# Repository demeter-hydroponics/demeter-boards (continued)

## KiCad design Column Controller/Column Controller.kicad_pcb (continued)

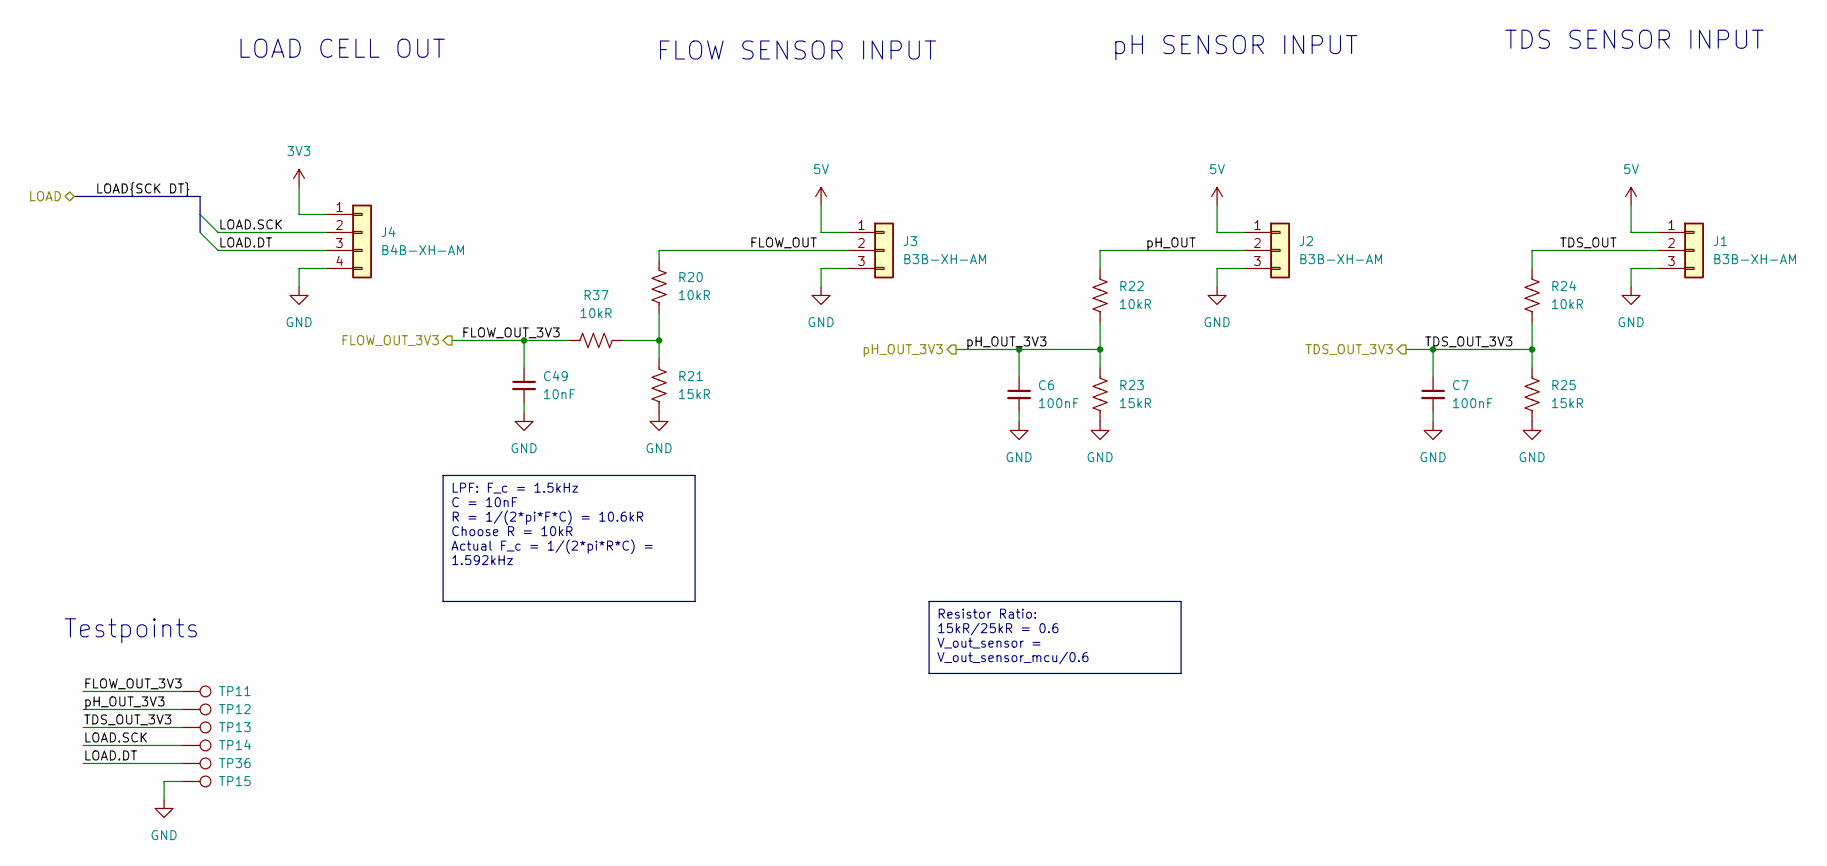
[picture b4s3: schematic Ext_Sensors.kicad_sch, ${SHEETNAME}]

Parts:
C6, C7: 100nF; C_0603_1608Metric; Part Number CL31B104KCFNNNE
C49: 10nF; C_0402_1005Metric; Part Number CL05B103KO5NNNC
J1, J2, J3: B3B-XH-AM; JST_XH_B3B-XH-AM_1x03_P2.50mm_Vertical; Part Number B3B-XH-AM
J4: B4B-XH-AM; JST_XH_B4B-XH-AM_1x04_P2.50mm_Vertical; Part Number B4B-XH-AM
R20, R22, R24, R37: 10kR; R_0603_1608Metric; Part Number RC0603FR-0710KL
R21, R23, R25: 15kR; R_0603_1608Metric; Part Number RC0603FR-0715KL
TP11, TP12, TP13, TP14, TP15, TP36: TestPoint_Pad_D1.0mm

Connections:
3V3: J4.1; also elsewhere on the board
5V: J1.1, J2.1, J3.1; also elsewhere on the board
/Ext Sensors/FLOW_OUT: J3.2, R20.1
/Ext Sensors/FLOW_OUT_3V3: C49.1, R37.1, TP11.1; also elsewhere on the board
/Ext Sensors/LOAD.DT: J4.3, TP36.1; also elsewhere on the board
/Ext Sensors/LOAD.SCK: J4.2, TP14.1; also elsewhere on the board
/Ext Sensors/TDS_OUT: J1.2, R24.1
/Ext Sensors/TDS_OUT_3V3: C7.1, R24.2, R25.1, TP13.1; also elsewhere on the board
/Ext Sensors/pH_OUT: J2.2, R22.1
/Ext Sensors/pH_OUT_3V3: C6.1, R22.2, R23.1, TP12.1; also elsewhere on the board
GND: C6.2, C7.2, C49.2, J1.3, J2.3, J3.3, J4.4, R21.2, R23.2, R25.2, TP15.1; also elsewhere on the board
unnamed: R20.2, R21.1, R37.2

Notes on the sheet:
LPF: F_c = 1.5kHz C = 10nF R = 1/(2*pi*F*C) = 10.6kR Choose R = 10kR Actual F_c = 1/(2*pi*R*C) = 1.592kHz
Resistor Ratio: 15kR/25kR = 0.6 V_out_sensor = V_out_sensor_mcu/0.6
Testpoints
pH SENSOR INPUT
FLOW SENSOR INPUT
LOAD CELL OUT
TDS SENSOR INPUT

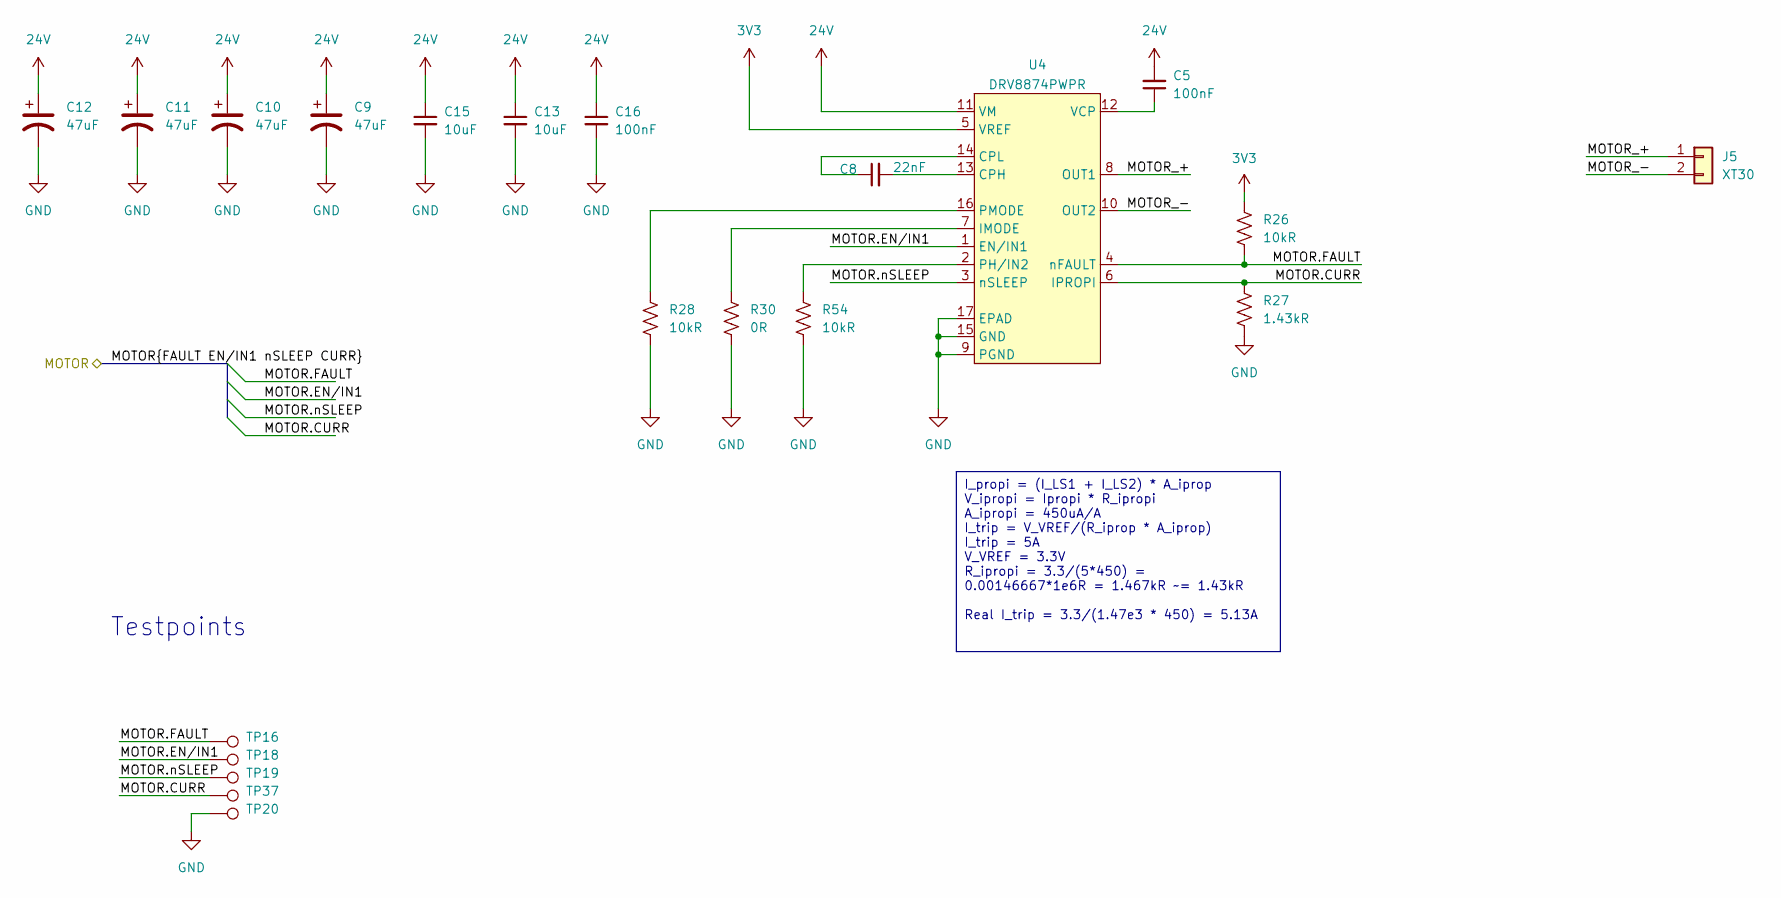
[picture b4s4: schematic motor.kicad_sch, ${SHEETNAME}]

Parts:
C5, C16: 100nF; C_0402_1005Metric; Part Number CL31B104KCFNNNE
C8: 22nF; C_0603_1608Metric
C9, C10, C11, C12: 47uF; CP_Radial_D8.0mm_P3.50mm; Part Number ECA-2AM470BJ
C13, C15: 10uF; C_1210_3225Metric; Part Number CL32B106KMVNNWE
J5: XT30
R26, R28, R54: 10kR; R_0603_1608Metric; Part Number RC0603FR-0710KL
R27: 1.43kR; R_0603_1608Metric; Part Number RC0603FR-071K43L
R30: 0R; R_0603_1608Metric; Part Number RC0603FR-070RL
TP16, TP18, TP19, TP20, TP37: TestPoint_Pad_D1.0mm
U4: DRV8874PWPR; DRV8874; Part Number DRV8874PWPR

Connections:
3V3: R26.1, U4.5 (VREF); also elsewhere on the board
24V: C5.2, C9.1, C10.1, C11.1, C12.1, C13.1, C15.1, C16.1, U4.11 (VM); also elsewhere on the board
/Microcontroller/MOTOR_2.CURR: R27.1, TP37.1, U4.6 (IPROPI); also elsewhere on the board
/Microcontroller/MOTOR_2.EN/IN1: TP18.1, U4.1 (EN/IN1); also elsewhere on the board
/Microcontroller/MOTOR_2.FAULT: R26.2, TP16.1, U4.4 (nFAULT); also elsewhere on the board
/Microcontroller/MOTOR_2.nSLEEP: TP19.1, U4.3 (nSLEEP); also elsewhere on the board
/Motor Controller 2/MOTOR_+: J5.1, U4.8 (OUT1)
/Motor Controller 2/MOTOR_-: J5.2, U4.10 (OUT2)
GND: C9.2, C10.2, C11.2, C12.2, C13.2, C15.2, C16.2, R27.2, R28.2, R30.2, R54.2, TP20.1, U4.9 (PGND), U4.15 (GND), U4.17 (EPAD); also elsewhere on the board
unnamed: C8.2, U4.13 (CPH)
unnamed: C8.1, U4.14 (CPL)
unnamed: R30.1, U4.7 (IMODE)
unnamed: R54.1, U4.2 (PH/IN2)
unnamed: R28.1, U4.16 (PMODE)
unnamed: C5.1, U4.12 (VCP)

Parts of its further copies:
C37, C38: 100nF; C_0402_1005Metric; Part Number CL31B104KCFNNNE
C39, C40, C41, C42: 47uF; CP_Radial_D8.0mm_P3.50mm; Part Number ECA-2AM470BJ
C43, C44: 10uF; C_1210_3225Metric; Part Number CL32B106KMVNNWE
C46: 22nF; C_0603_1608Metric
J9: XT30
R29, R55, R58: 10kR; R_0603_1608Metric; Part Number RC0603FR-0710KL
R60: 0R; R_0603_1608Metric; Part Number RC0603FR-070RL
R61: 1.43kR; R_0603_1608Metric; Part Number RC0603FR-071K43L
TP21, TP23, TP24, TP25, TP38: TestPoint_Pad_D1.0mm
U10: DRV8874PWPR; DRV8874; Part Number DRV8874PWPR

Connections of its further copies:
3V3: R58.1, U10.5 (VREF); also elsewhere on the board
24V: C37.2, C38.1, C39.1, C40.1, C41.1, C42.1, C43.1, C44.1, U10.11 (VM); also elsewhere on the board
/Microcontroller/MOTOR_1.CURR: R61.1, TP38.1, U10.6 (IPROPI); also elsewhere on the board
/Microcontroller/MOTOR_1.EN/IN1: TP23.1, U10.1 (EN/IN1); also elsewhere on the board
/Microcontroller/MOTOR_1.FAULT: R58.2, TP21.1, U10.4 (nFAULT); also elsewhere on the board
/Microcontroller/MOTOR_1.nSLEEP: TP24.1, U10.3 (nSLEEP); also elsewhere on the board
/Motor Controller 1/MOTOR_+: J9.1, U10.8 (OUT1)
/Motor Controller 1/MOTOR_-: J9.2, U10.10 (OUT2)
GND: C38.2, C39.2, C40.2, C41.2, C42.2, C43.2, C44.2, R29.2, R55.2, R60.2, R61.2, TP25.1, U10.9 (PGND), U10.15 (GND), U10.17 (EPAD); also elsewhere on the board
unnamed: C46.2, U10.13 (CPH)
unnamed: C46.1, U10.14 (CPL)
unnamed: R60.1, U10.7 (IMODE)
unnamed: R55.1, U10.2 (PH/IN2)
unnamed: R29.1, U10.16 (PMODE)
unnamed: C37.1, U10.12 (VCP)

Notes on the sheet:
I_propi = (I_LS1 + I_LS2) * A_iprop V_ipropi = Ipropi * R_ipropi A_ipropi = 450uA/A I_trip = V_VREF/(R_iprop * A_iprop) I_trip = 5A V_VREF = 3.3V R_ipropi = 3.3/(5*450) = 0.00146667*1e6R = 1.467kR ~= 1.43kR Real I_trip = 3.3/(1.47e3 * 450) = 5.13A
Testpoints

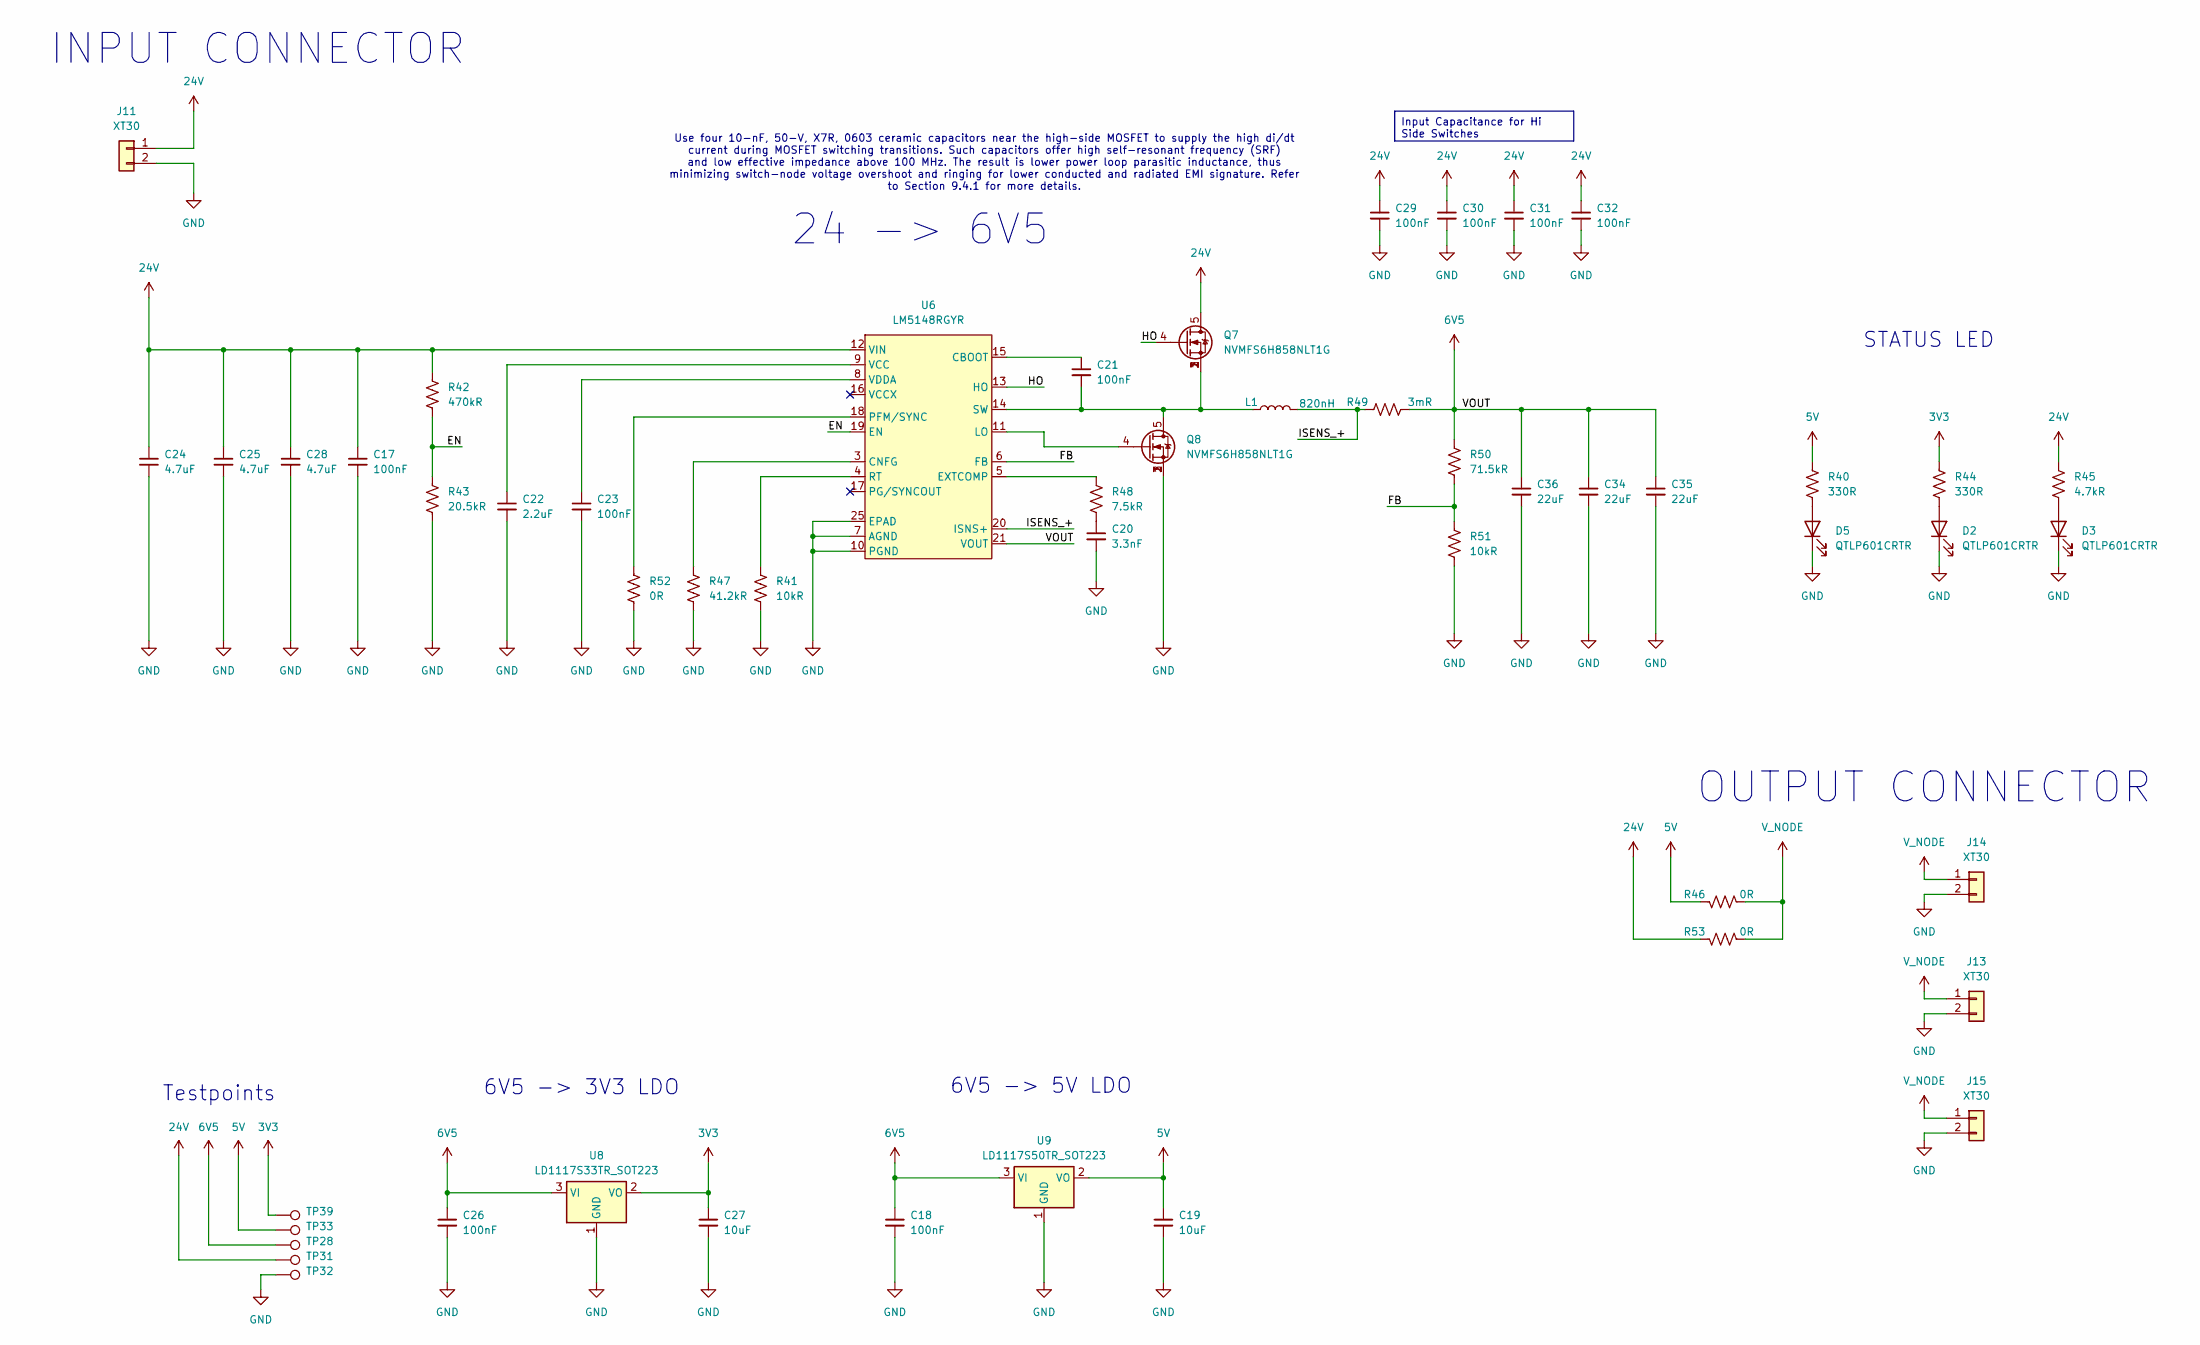
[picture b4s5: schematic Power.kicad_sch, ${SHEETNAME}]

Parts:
C17, C21, C23, C29, C30, C31, C32: 100nF; C_0402_1005Metric; Part Number CL31B104KCFNNNE
C18, C26: 100nF; C_1206_3216Metric; Part Number CL31B104KCFNNNE
C19, C27: 10uF; C_1210_3225Metric; Part Number CL32B106KMVNNWE
C20: 3.3nF; C_0402_1005Metric; Part Number CL05B332KA5VPNC
C22: 2.2uF; C_0603_1608Metric; Part Number GRM188R61H225KE11D
C24, C25, C28: 4.7uF; C_1210_3225Metric; Part Number CL32Y475MCIVPNE
C34, C35, C36: 22uF; C_0805_2012Metric; Part Number CL21A226MAYNNNE
D2, D3, D5: QTLP601CRTR; LED_0603_1608Metric; Part Number QTLP601CRTR
J11, J13, J14, J15: XT30; Part Number XT30
L1: 820nH; SRP7050; Part Number SRP7050TA-R82M
Q7, Q8: NVMFS6H858NLT1G; NVMFS6H858NL
R40, R44: 330R; R_0402_1005Metric; Part Number RC0603FR-07330RL
R41, R51: 10kR; R_0603_1608Metric; Part Number RC0603FR-0710KL
R42: 470kR; R_0603_1608Metric; Part Number RC0603FR-07470KL
R43: 20.5kR; R_0603_1608Metric; Part Number RC0603FR-0720K5L
R45: 4.7kR; R_0603_1608Metric; Part Number RC0603FR-074K7L
R46, R52, R53: 0R; R_0603_1608Metric; Part Number RC0603FR-070RL
R47: 41.2kR; R_0603_1608Metric; Part Number RC0603FR-0741K2L
R48: 7.5kR; R_0603_1608Metric; Part Number RC0603FR-077K5L
R49: 3mR; R_0805_2012Metric; Part Number PA0805FRF070R003L
R50: 71.5kR; R_0603_1608Metric; Part Number RC0603FR-0771K5L
TP28, TP31, TP32, TP33, TP39: TestPoint_Pad_D1.0mm
U6: LM5148RGYR; LM5148
U8: LD1117S33TR_SOT223; SOT-223-3_TabPin2; Part Number LD1117S33TR_SOT223
U9: LD1117S50TR_SOT223; SOT-223-3_TabPin2; Part Number LD1117S50TR_SOT223

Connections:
3V3: C27.1, R44.2, TP39.1, U8.2 (VO); also elsewhere on the board
5V: C19.1, R40.2, R46.2, TP33.1, U9.2 (VO); also elsewhere on the board
6V5: C18.1, C26.1, C34.1, C35.1, C36.1, R49.2, R50.2, TP28.1, U6.21 (VOUT), U8.3 (VI), U9.3 (VI)
24V: C17.1, C24.1, C25.1, C28.1, C29.1, C30.1, C31.1, C32.1, J11.1, Q7.5, R42.2, R45.2, R53.2, TP31.1, U6.12 (VIN); also elsewhere on the board
/Power/EN: R42.1, R43.2, U6.19 (EN)
/Power/FB: R50.1, R51.2, U6.6 (FB)
/Power/HO: Q7.4, U6.13 (HO)
/Power/ISENS_+: L1.2, R49.1, U6.20 (ISNS+)
GND: C17.2, C18.2, C19.2, C20.2, C22.2, C23.2, C24.2, C25.2, C26.2, C27.2, C28.2, C29.2, C30.2, C31.2, C32.2, C34.2, C35.2, C36.2, D2.1 (K), D3.1 (K), D5.1 (K), J11.2, J13.2, J14.2, J15.2, Q8.1, Q8.2, Q8.3, R41.1, R43.1, R47.1, R51.1, R52.1, TP32.1, U6.7 (AGND), U6.10 (PGND), U6.25 (EPAD), U8.1 (GND), U9.1 (GND); also elsewhere on the board
unnamed: C20.1, R48.1
unnamed: D2.2 (A), R44.1
unnamed: D3.2 (A), R45.1
unnamed: D5.2 (A), R40.1
unnamed: C21.1, U6.15 (CBOOT)
unnamed: R47.2, U6.3 (CNFG)
unnamed: R48.2, U6.5 (EXTCOMP)
unnamed: Q8.4, U6.11 (LO)
unnamed: R52.2, U6.18 (PFM/SYNC)
unnamed: R41.2, U6.4 (RT)
unnamed: C21.2, L1.1, Q7.1, Q7.2, Q7.3, Q8.5, U6.14 (SW)
unnamed: C22.1, U6.9 (VCC)
unnamed: C23.1, U6.8 (VDDA)
V_NODE: J13.1, J14.1, J15.1, R46.1, R53.1

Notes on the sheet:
Input Capacitance for Hi Side Switches
Use four 10-nF, 50-V, X7R, 0603 ceramic capacitors near the high-side MOSFET to supply the high di/dt current during MOSFET switching transitions. Such capacitors offer high self-resonant frequency (SRF) and low effective impedance above 100 MHz. The result is lower power loop parasitic inductance,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
Testpoints
6V5 -> 3V3 LDO
OUTPUT CONNECTOR
INPUT CONNECTOR
24 -> 6V5
STATUS LED
6V5 -> 5V LDO

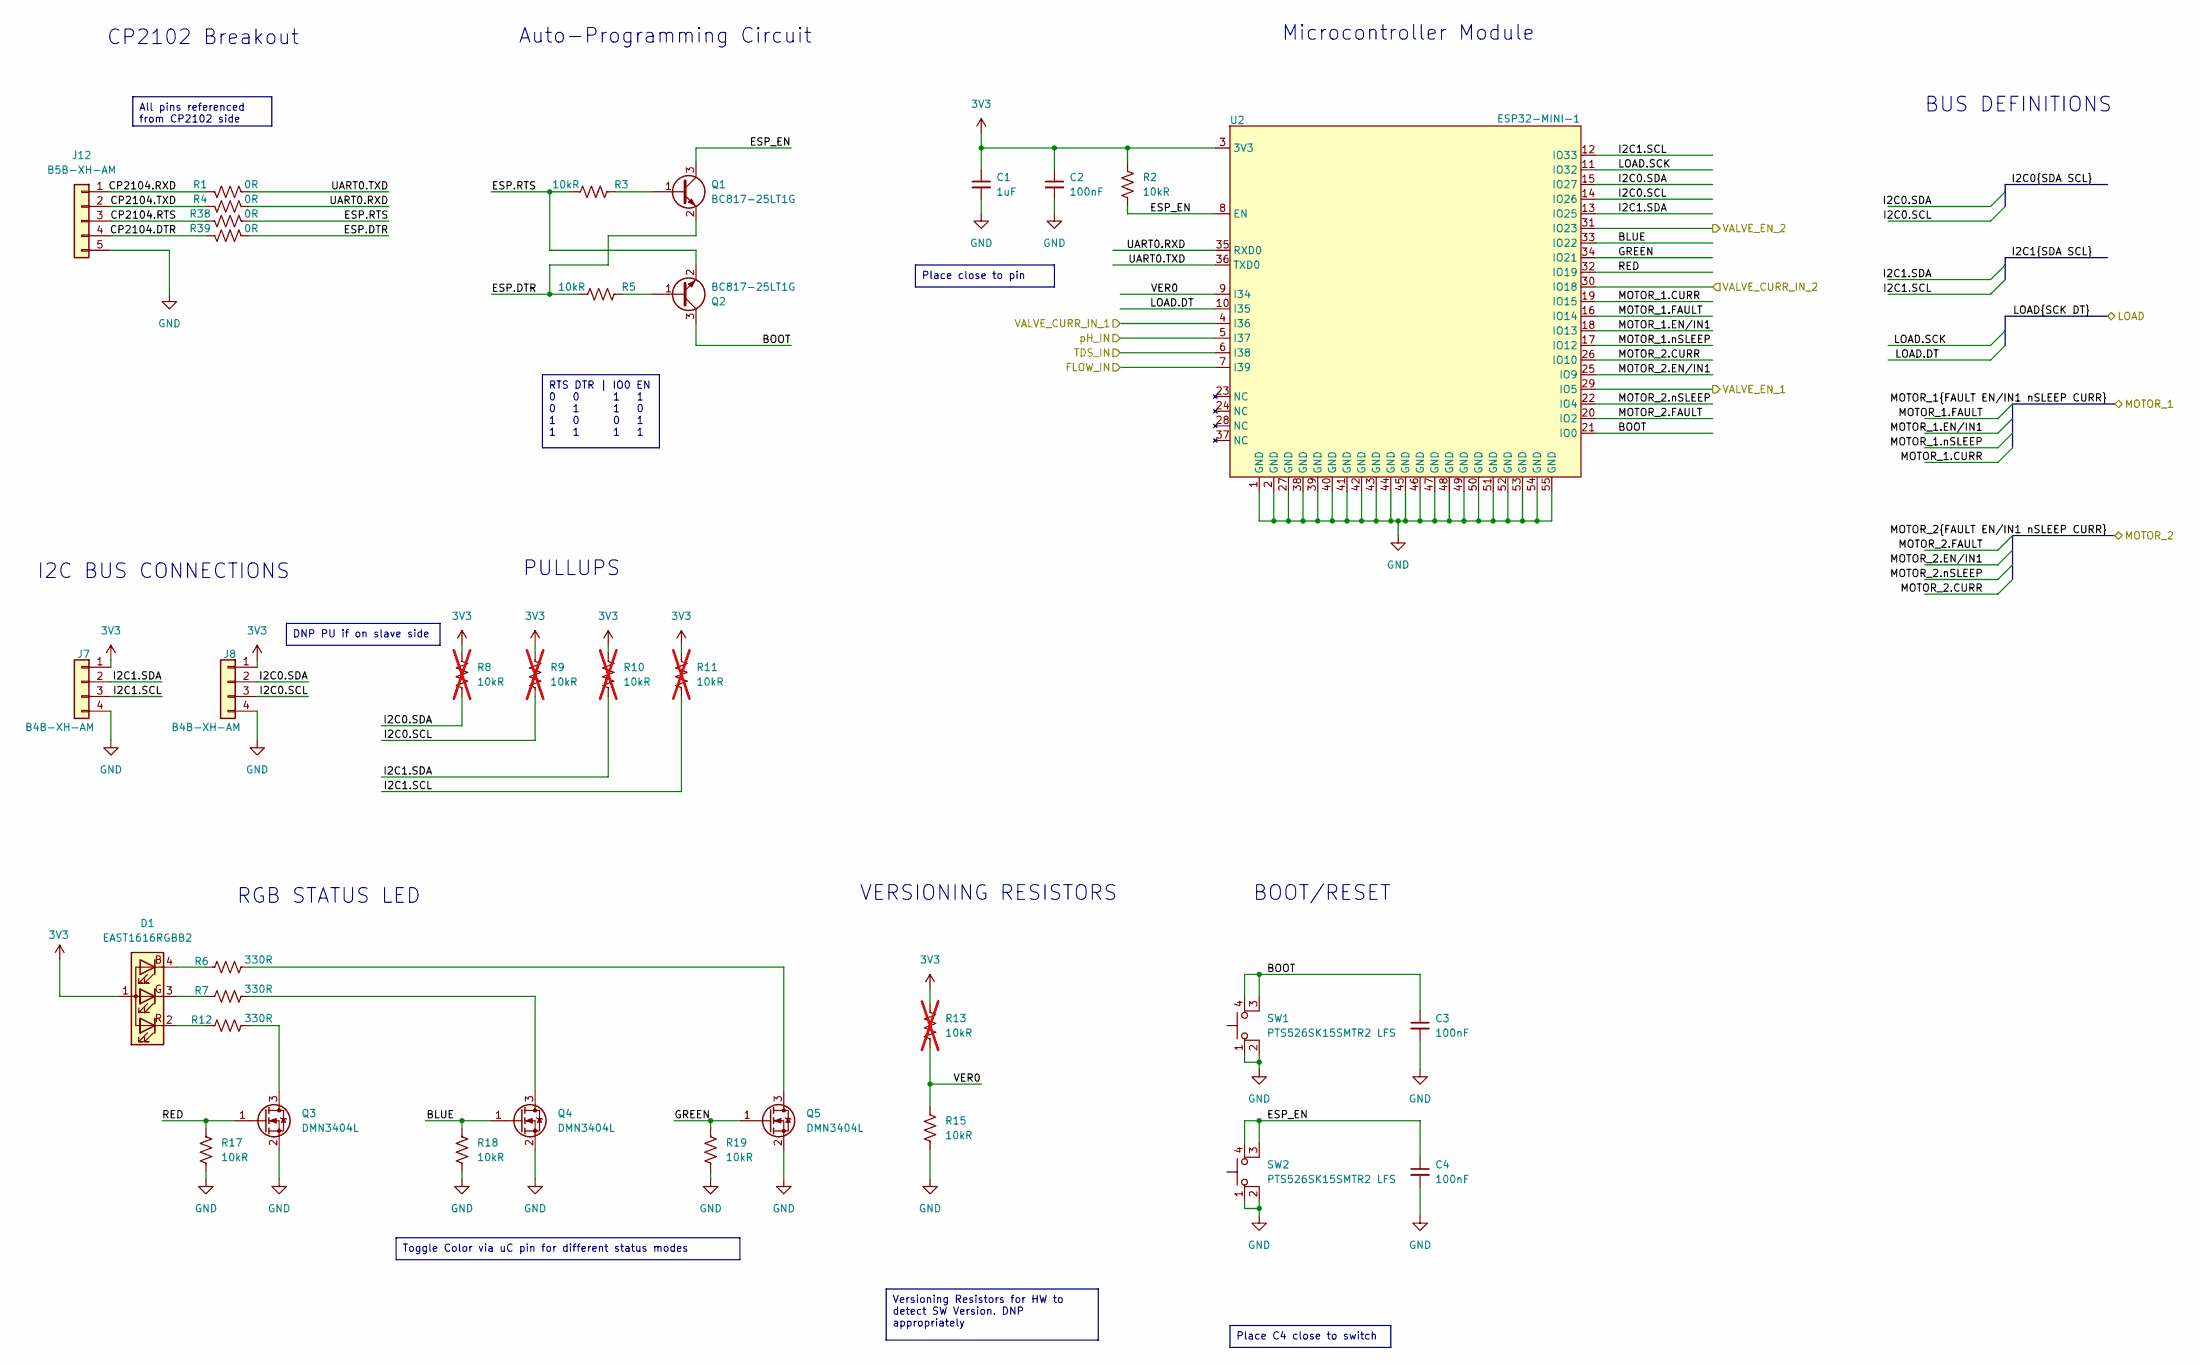
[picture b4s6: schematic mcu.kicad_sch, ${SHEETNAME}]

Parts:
C1: 1uF; C_1206_3216Metric; Part Number CL31B105KCHNNNE
C2, C3, C4: 100nF; C_1206_3216Metric; Part Number CL31B104KCFNNNE
D1: EAST1616RGBB2; Part Number EAST1616RGBB2
J7, J8: B4B-XH-AM; JST_XH_B4B-XH-AM_1x04_P2.50mm_Vertical; Part Number B4B-XH-AM
J12: B5B-XH-AM; JST_XH_B5B-XH-AM_1x05_P2.50mm_Vertical
Q1, Q2: BC817-25LT1G; SOT-23; Part Number BC817-25LT1G
Q3, Q4, Q5: DMN3404L; SOT-23; Part Number DMN3404L
R1, R4, R38, R39: 0R; R_0603_1608Metric; Part Number RC0603FR-070RL
R2, R3, R5, R15, R17, R18, R19: 10kR; R_0603_1608Metric; Part Number RC0603FR-0710KL
R6, R7, R12: 330R; R_0402_1005Metric; Part Number RC0603FR-07330RL
R8, R9, R10, R11, R13: 10kR; R_0603_1608Metric; Part Number RC0603FR-0710KL; not fitted
SW1, SW2: PTS526SK15SMTR2 LFS; Part Number PTS526SK15SMTR2 LFS
U2: ESP32-MINI-1

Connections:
3V3: C1.1, C2.1, D1.1 (A), J7.1, J8.1, R2.1, R8.1, R9.1, R10.1, R11.1, R13.1, U2.3 (3V3); also elsewhere on the board
/Ext Sensors/FLOW_OUT_3V3: U2.7 (I39); also elsewhere on the board
/Ext Sensors/LOAD.DT: U2.10 (I35); also elsewhere on the board
/Ext Sensors/LOAD.SCK: U2.11 (IO32); also elsewhere on the board
/Ext Sensors/TDS_OUT_3V3: U2.6 (I38); also elsewhere on the board
/Ext Sensors/pH_OUT_3V3: U2.5 (I37); also elsewhere on the board
/Microcontroller/BLUE: Q4.1 (G), R18.1, U2.33 (IO22)
/Microcontroller/BOOT: C3.1, Q2.3 (C), SW1.3 (K), SW1.4 (A), U2.21 (IO0)
/Microcontroller/CP2104.DTR: J12.4, R39.2
/Microcontroller/CP2104.RTS: J12.3, R38.2
/Microcontroller/CP2104.RXD: J12.1, R1.2
/Microcontroller/CP2104.TXD: J12.2, R4.2
/Microcontroller/ESP.DTR: Q1.2 (E), R5.1, R39.1
/Microcontroller/ESP.RTS: Q2.2 (E), R3.1, R38.1
/Microcontroller/ESP_EN: C4.1, Q1.3 (C), R2.2, SW2.3 (K), SW2.4 (A), U2.8 (EN)
/Microcontroller/GREEN: Q5.1 (G), R19.1, U2.34 (IO21)
/Microcontroller/I2C0.SCL: J8.3, R9.2, U2.14 (IO26)
/Microcontroller/I2C0.SDA: J8.2, R8.2, U2.15 (IO27)
/Microcontroller/I2C1.SCL: J7.3, R11.2, U2.12 (IO33)
/Microcontroller/I2C1.SDA: J7.2, R10.2, U2.13 (IO25)
/Microcontroller/MOTOR_1.CURR: U2.19 (IO15); also elsewhere on the board
/Microcontroller/MOTOR_1.EN/IN1: U2.18 (IO13); also elsewhere on the board
/Microcontroller/MOTOR_1.FAULT: U2.16 (IO14); also elsewhere on the board
/Microcontroller/MOTOR_1.nSLEEP: U2.17 (IO12); also elsewhere on the board
/Microcontroller/MOTOR_2.CURR: U2.26 (IO10); also elsewhere on the board
/Microcontroller/MOTOR_2.EN/IN1: U2.25 (IO9); also elsewhere on the board
/Microcontroller/MOTOR_2.FAULT: U2.20 (IO2); also elsewhere on the board
/Microcontroller/MOTOR_2.nSLEEP: U2.22 (IO4); also elsewhere on the board
/Microcontroller/RED: Q3.1 (G), R17.1, U2.32 (IO19)
/Microcontroller/UART0.RXD: R4.1, U2.35 (RXD0)
/Microcontroller/UART0.TXD: R1.1, U2.36 (TXD0)
/Microcontroller/VER0: R13.2, R15.1, U2.9 (I34)
/Relay Controller 1/CURR_OUT: U2.4 (I36); also elsewhere on the board
/Relay Controller 1/RELAY_IN: U2.29 (IO5); also elsewhere on the board
/Relay Controller 2/CURR_OUT: U2.30 (IO18); also elsewhere on the board
/Relay Controller 2/RELAY_IN: U2.31 (IO23); also elsewhere on the board
GND: C1.2, C2.2, C3.2, C4.2, J7.4, J8.4, J12.5, Q3.2 (S), Q4.2 (S), Q5.2 (S), R15.2, R17.2, R18.2, R19.2, SW1.1, SW1.2, SW2.1, SW2.2, U2.1 (GND), U2.2 (GND), U2.27 (GND), U2.38 (GND), U2.39 (GND), U2.40 (GND), U2.41 (GND), U2.42 (GND), U2.43 (GND), U2.44 (GND), U2.45 (GND), U2.46 (GND), U2.47 (GND), U2.48 (GND), U2.49 (GND), U2.50 (GND), U2.51 (GND), U2.52 (GND), U2.53 (GND), U2.54 (GND), U2.55 (GND); also elsewhere on the board
unnamed: D1.4 (BK), R6.1
unnamed: D1.3 (GK), R7.1
unnamed: D1.2 (RK), R12.1
unnamed: Q1.1 (B), R3.2
unnamed: Q2.1 (B), R5.2
unnamed: Q3.3 (D), R12.2
unnamed: Q4.3 (D), R7.2
unnamed: Q5.3 (D), R6.2

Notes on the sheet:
DNP PU if on slave side
All pins referenced from CP2102 side
Versioning Resistors for HW to detect SW Version. DNP appropriately
RTS DTR | IO0 EN 0 0 1 1 0 1 1 0 1 0 0 1 1 1 1 1
Toggle Color via uC pin for different status modes
Place C4 close to switch
Place close to pin
I2C BUS CONNECTIONS
VERSIONING RESISTORS
RGB STATUS LED
Microcontroller Module
PULLUPS
Auto-Programming Circuit
CP2102 Breakout
BUS DEFINITIONS
BOOT/RESET

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
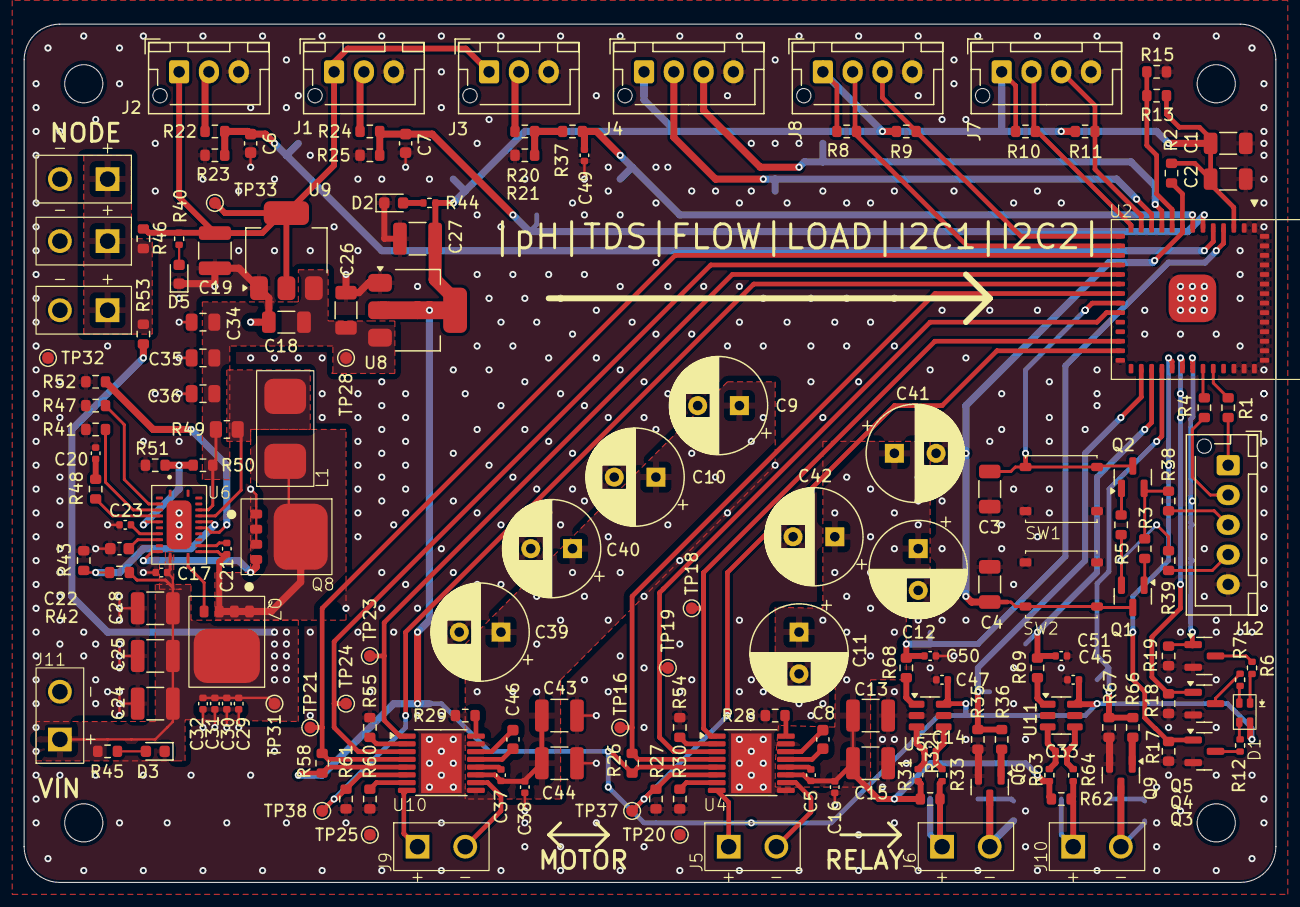
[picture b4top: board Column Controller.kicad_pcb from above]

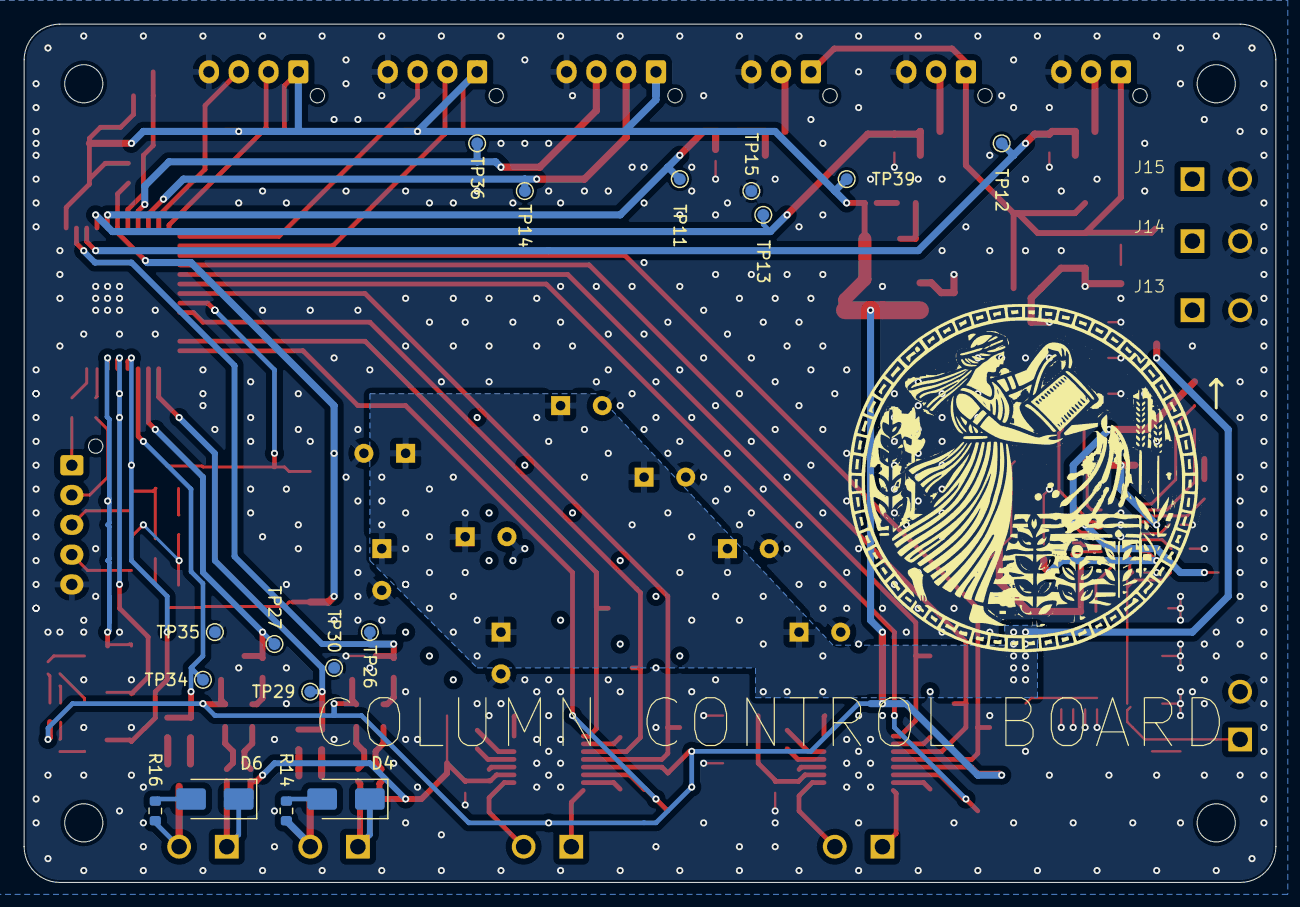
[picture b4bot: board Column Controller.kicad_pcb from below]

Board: 4 copper layers, 105.0 x 72.0 mm, 186 parts (17 on the bottom side), 100 nets.

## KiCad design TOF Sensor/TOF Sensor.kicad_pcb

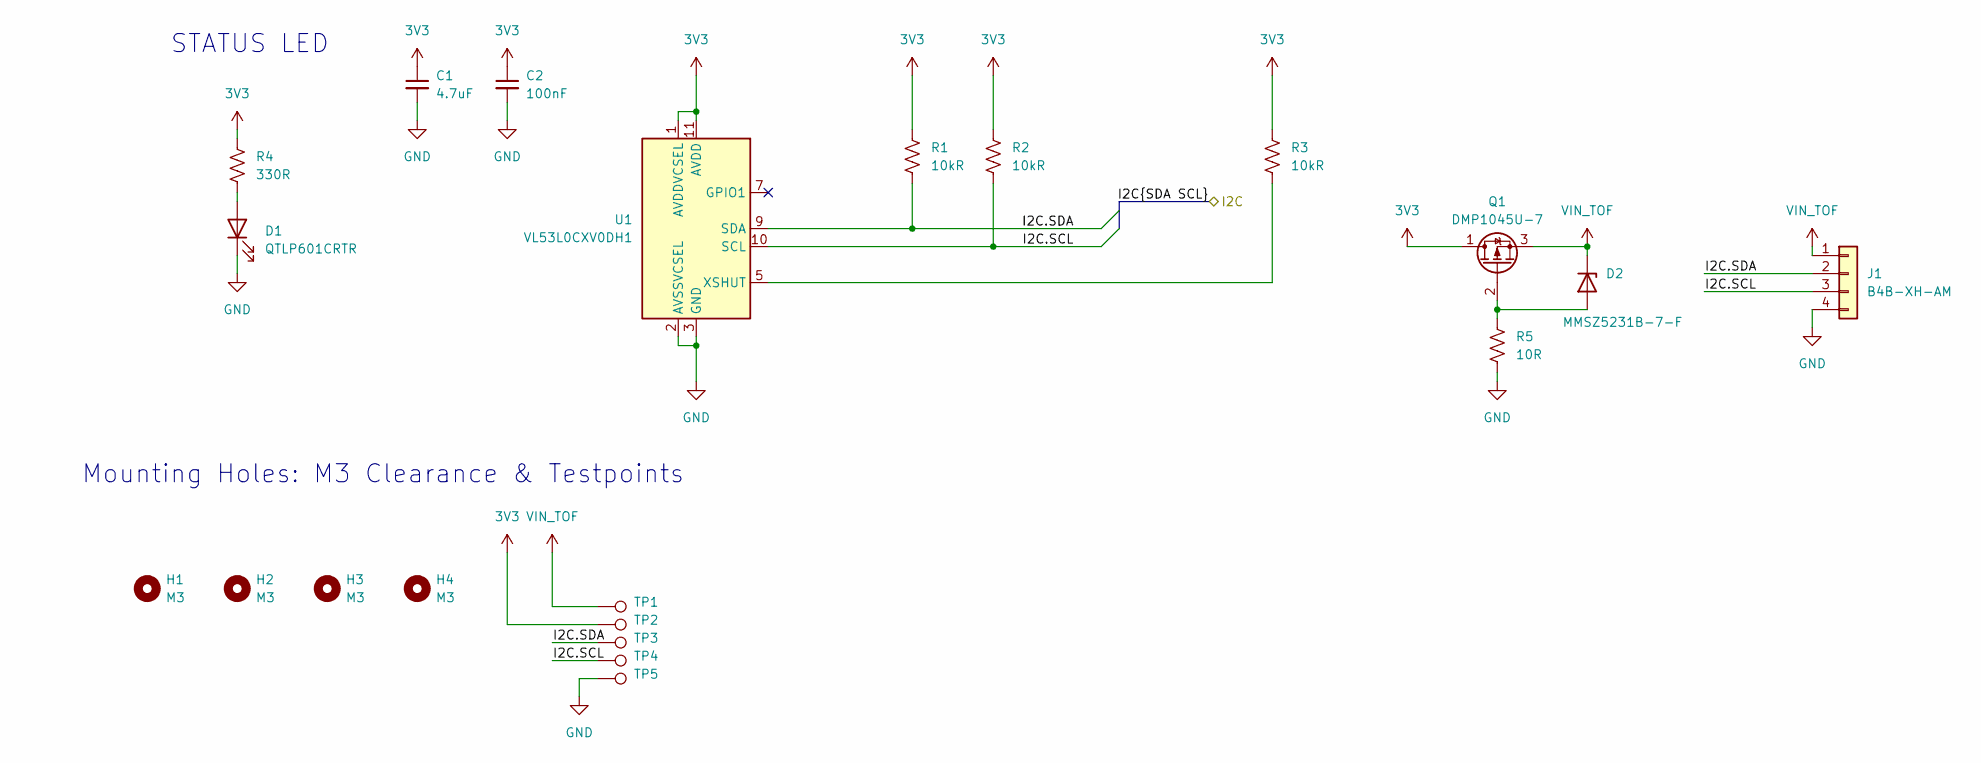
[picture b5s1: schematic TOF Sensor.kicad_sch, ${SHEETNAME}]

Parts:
C1: 4.7uF; C_1210_3225Metric; Part Number CL32Y475MCIVPNE
C2: 100nF; C_1206_3216Metric; Part Number CL31B104KCFNNNE
D1: QTLP601CRTR; LED_0603_1608Metric; Part Number QTLP601CRTR
D2: MMSZ5231B-7-F; D_SOD-123; Part Number MMSZ5231B-7-F
H1, H2, H3, H4: M3; MountingHole_3.2mm_M3
J1: B4B-XH-AM; JST_XH_B4B-XH-AM_1x04_P2.50mm_Vertical; Part Number B4B-XH-AM
Q1: DMP1045U-7; SOT-23-3; Part Number DMP1045U-7
R1, R2, R3: 10kR; R_0603_1608Metric; Part Number RC0603FR-0710KL
R4: 330R; R_0402_1005Metric; Part Number RC0603FR-07330RL
R5: 10R; R_0402_1005Metric; Part Number RC0603FR-0710RL
TP1, TP2, TP3, TP4, TP5: TestPoint_Pad_D1.0mm
U1: VL53L0CXV0DH1; ST_VL53L1x; Part Number VL53L0X

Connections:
3V3: C1.1, C2.1, Q1.1 (D), R1.1, R2.1, R3.1, R4.2, TP2.1, U1.1 (AVDDVCSEL), U1.11 (AVDD)
/I2C.SCL: J1.3, R2.2, TP4.1, U1.10 (SCL)
/I2C.SDA: J1.2, R1.2, TP3.1, U1.9 (SDA)
GND: C1.2, C2.2, D1.1 (K), J1.4, R5.2, TP5.1, U1.2 (AVSSVCSEL), U1.3 (GND), U1.4 (GND), U1.6 (GND), U1.12 (GND)
unnamed: D1.2 (A), R4.1
unnamed: D2.2 (A), Q1.2 (G), R5.1
unnamed: R3.2, U1.5 (XSHUT)
VIN_TOF: D2.1 (K), J1.1, Q1.3 (S), TP1.1

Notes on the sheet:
STATUS LED
Mounting Holes: M3 Clearance & Testpoints

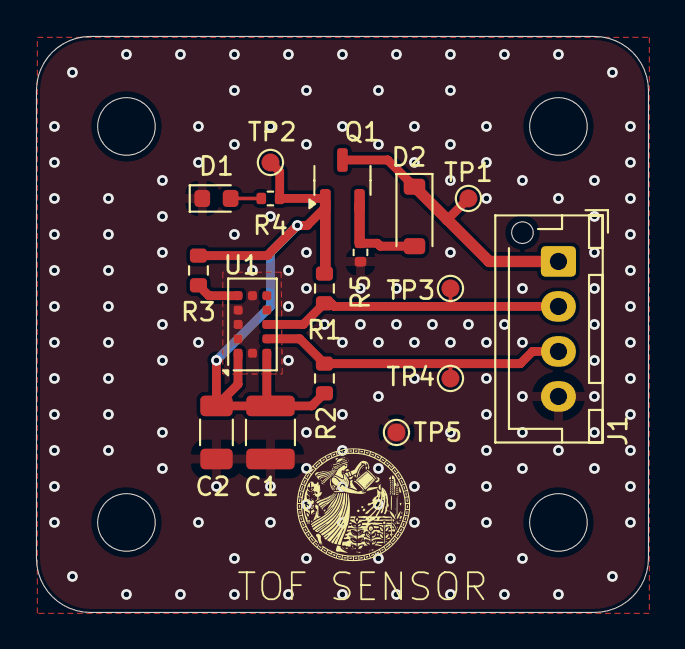
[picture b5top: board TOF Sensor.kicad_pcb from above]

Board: 4 copper layers, 34.0 x 32.0 mm, 21 parts (0 on the bottom side), 8 nets.

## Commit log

2024-12-19 Board backed up
2024-12-19 Update README.md
    Added more info
2024-12-26 Updated 3V3 rail on column board
2024-12-26 Added fab outputs and step files
2025-01-10 adding board as sldw file
2025-01-10 lumen sensor sldprt
